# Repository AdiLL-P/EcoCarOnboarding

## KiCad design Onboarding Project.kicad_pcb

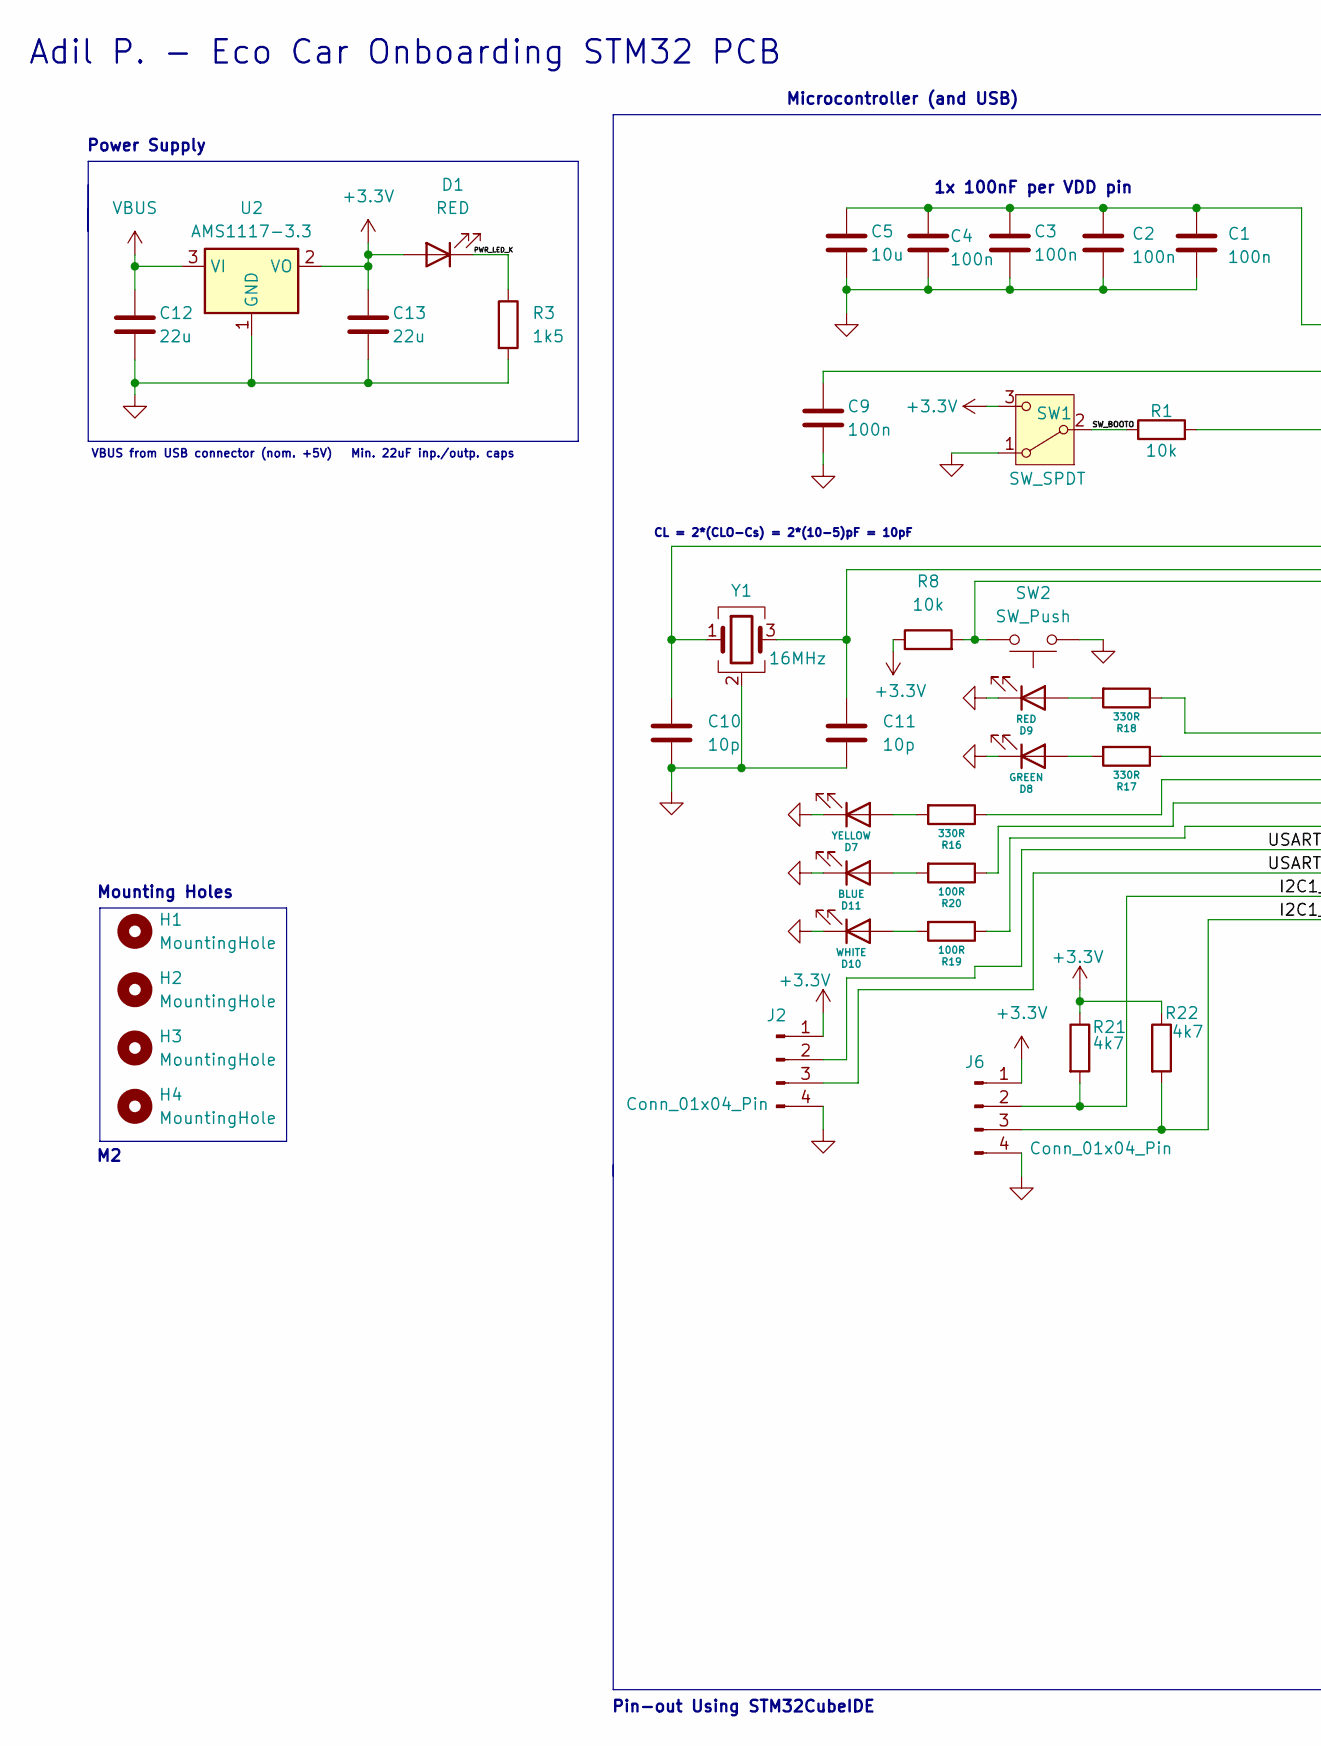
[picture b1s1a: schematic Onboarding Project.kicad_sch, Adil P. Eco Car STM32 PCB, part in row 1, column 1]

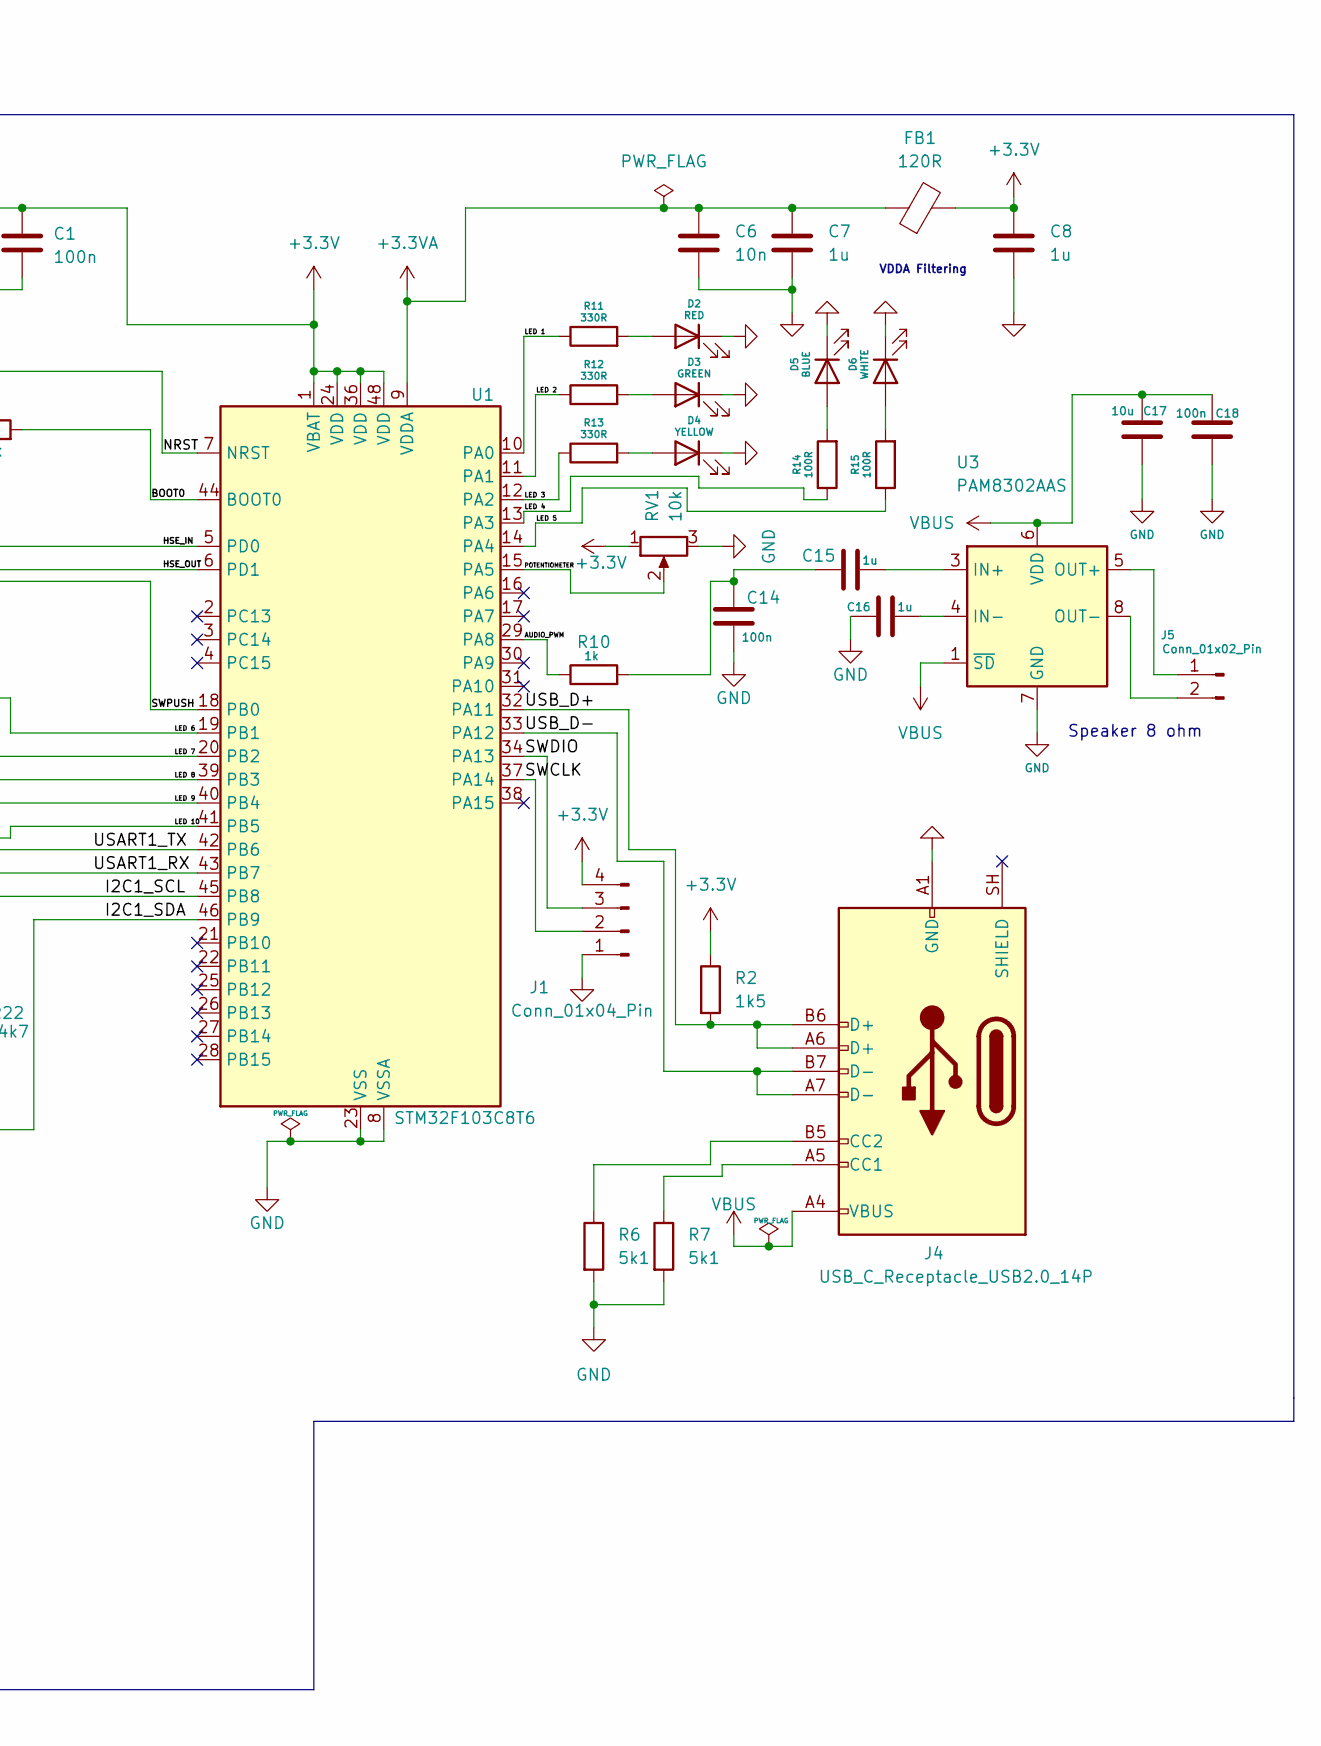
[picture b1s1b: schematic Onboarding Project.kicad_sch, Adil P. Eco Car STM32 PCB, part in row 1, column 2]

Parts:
C1, C2, C3, C4, C9, C14, C18: 100n; C_0402_1005Metric
C5, C17: 10u; C_0603_1608Metric
C6: 10n; C_0402_1005Metric
C7, C8, C15, C16: 1u; C_0402_1005Metric
C10, C11: 10p; C_0402_1005Metric
C12, C13: 22u; C_0805_2012Metric
D1, D2, D9: RED; LED_0603_1608Metric
D3, D8: GREEN; LED_0603_1608Metric
D4, D7: YELLOW; LED_0603_1608Metric
D5, D11: BLUE; LED_0603_1608Metric
D6, D10: WHITE; LED_0603_1608Metric
FB1: 120R; L_0603_1608Metric
H1, H2, H3, H4: MountingHole; MountingHole_2.2mm_M2
J1, J2, J6: Conn_01x04_Pin; PinHeader_1x04_P2.54mm_Vertical
J4: USB_C_Receptacle_USB2.0_14P; USB_C_Receptacle_HRO_TYPE-C-31-M-12
J5: Conn_01x02_Pin; PinHeader_1x02_P2.54mm_Vertical
R1, R8: 10k; R_0402_1005Metric
R2, R3: 1k5; R_0402_1005Metric
R6, R7: 5k1; R_0402_1005Metric
R10: 1k; R_0402_1005Metric
R11, R12, R13, R16, R17, R18: 330R; R_0603_1608Metric
R14, R15, R19, R20: 100R; R_0603_1608Metric
R21, R22: 4k7; R_0603_1608Metric
RV1: 10k; TSSOP-14_4.4x5mm_P0.65mm
SW1: SW_SPDT; SW_SPDT_PCM12
SW2: SW_Push; SW_NKK_GW12LJP
U1: STM32F103C8T6; LQFP-48_7x7mm_P0.5mm
U2: AMS1117-3.3; SOT-223-3_TabPin2
U3: PAM8302AAS; SOIC-8_3.9x4.9mm_P1.27mm
Y1: 16MHz; Crystal_SMD_3225-4Pin_3.2x2.5mm

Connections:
+3.3V: C1.1, C2.1, C3.1, C4.1, C5.1, C8.1, C13.1, D1.2 (A), FB1.2, J1.4, J2.1, J6.1, R2.1, R8.1, R21.1, R22.1, RV1.1, SW1.3 (C), U1.1 (VBAT), U1.24 (VDD), U1.36 (VDD), U1.48 (VDD), U2.2 (VO)
+3.3VA: C6.1, C7.1, FB1.1, U1.9 (VDDA)
/AUDIO_PWM: R10.1, U1.29 (PA8)
/BOOT0: R1.2, U1.44 (BOOT0)
/HSE_IN: C10.1, U1.5 (PD0), Y1.1
/HSE_OUT: C11.1, U1.6 (PD1), Y1.3
/I2C1_SCL: J6.2, R21.2, U1.45 (PB8)
/I2C1_SDA: J6.3, R22.2, U1.46 (PB9)
/LED 1: R11.1, U1.10 (PA0)
/LED 2: R12.1, U1.11 (PA1)
/LED 3: R13.1, U1.12 (PA2)
/LED 4: R14.1, U1.13 (PA3)
/LED 5: R15.1, U1.14 (PA4)
/LED 6: R18.1, U1.19 (PB1)
/LED 7: R17.1, U1.20 (PB2)
/LED 8: R16.1, U1.39 (PB3)
/LED 9: R20.1, U1.40 (PB4)
/LED 10: R19.1, U1.41 (PB5)
/NRST: C9.1, U1.7 (NRST)
/POTENTIOMETER: RV1.2, U1.15 (PA5)
/PWR_LED_K: D1.1 (K), R3.1
/SWCLK: J1.2, U1.37 (PA14)
/SWDIO: J1.3, U1.34 (PA13)
/SWPUSH: R8.2, SW2.2, U1.18 (PB0)
/SW_BOOTO: R1.1, SW1.2 (B)
/USART1_RX: J2.3, U1.43 (PB7)
/USART1_TX: J2.2, U1.42 (PB6)
/USB_D+: J4.A6 (D+), J4.B6 (D+), R2.2, U1.32 (PA11)
/USB_D-: J4.A7 (D-), J4.B7 (D-), U1.33 (PA12)
GND: C1.2, C2.2, C3.2, C4.2, C5.2, C6.2, C7.2, C8.2, C9.2, C10.2, C11.2, C12.2, C13.2, C14.2, C16.1, C17.1, C18.1, D2.1 (K), D3.1 (K), D4.1 (K), D5.1 (K), D6.1 (K), D7.1 (K), D8.1 (K), D9.1 (K), D10.1 (K), D11.1 (K), J1.1, J2.4, J4.A1 (GND), J4.A12 (GND), J4.B1 (GND), J4.B12 (GND), J6.4, R3.2, R6.2, R7.2, RV1.3, SW1.1 (A), SW2.1, U1.8 (VSSA), U1.23 (VSS), U1.35 (VSS), U1.47 (VSS), U2.1 (GND), U3.7 (GND), Y1.2 (G), Y1.4 (G)
unnamed: C14.1, C15.1, R10.2
unnamed: D2.2 (A), R11.2
unnamed: D3.2 (A), R12.2
unnamed: D4.2 (A), R13.2
unnamed: D5.2 (A), R14.2
unnamed: D6.2 (A), R15.2
unnamed: D7.2 (A), R16.2
unnamed: D8.2 (A), R17.2
unnamed: D9.2 (A), R18.2
unnamed: D10.2 (A), R19.2
unnamed: D11.2 (A), R20.2
unnamed: J4.A5 (CC1), R7.1
unnamed: J4.B5 (CC2), R6.1
unnamed: J5.1, U3.5 (OUT+)
unnamed: J5.2, U3.8 (OUT-)
unnamed: C15.2, U3.3 (IN+)
unnamed: C16.2, U3.4 (IN-)
VBUS: C12.1, C17.2, C18.2, J4.A4 (VBUS), J4.A9 (VBUS), J4.B4 (VBUS), J4.B9 (VBUS), U2.3 (VI), U3.1 (~SD), U3.6 (VDD)

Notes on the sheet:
Pin-out Using STM32CubeIDE
Adil P. - Eco Car Onboarding STM32 PCB
1x 100nF per VDD pin
Mounting Holes
Speaker 8 ohm
Microcontroller (and USB)
Power Supply
VDDA Filtering
CL = 2*(CLO-Cs) = 2*(10-5)pF = 10pF
VBUS from USB connector (nom. +5V) Min. 22uF inp./outp. caps

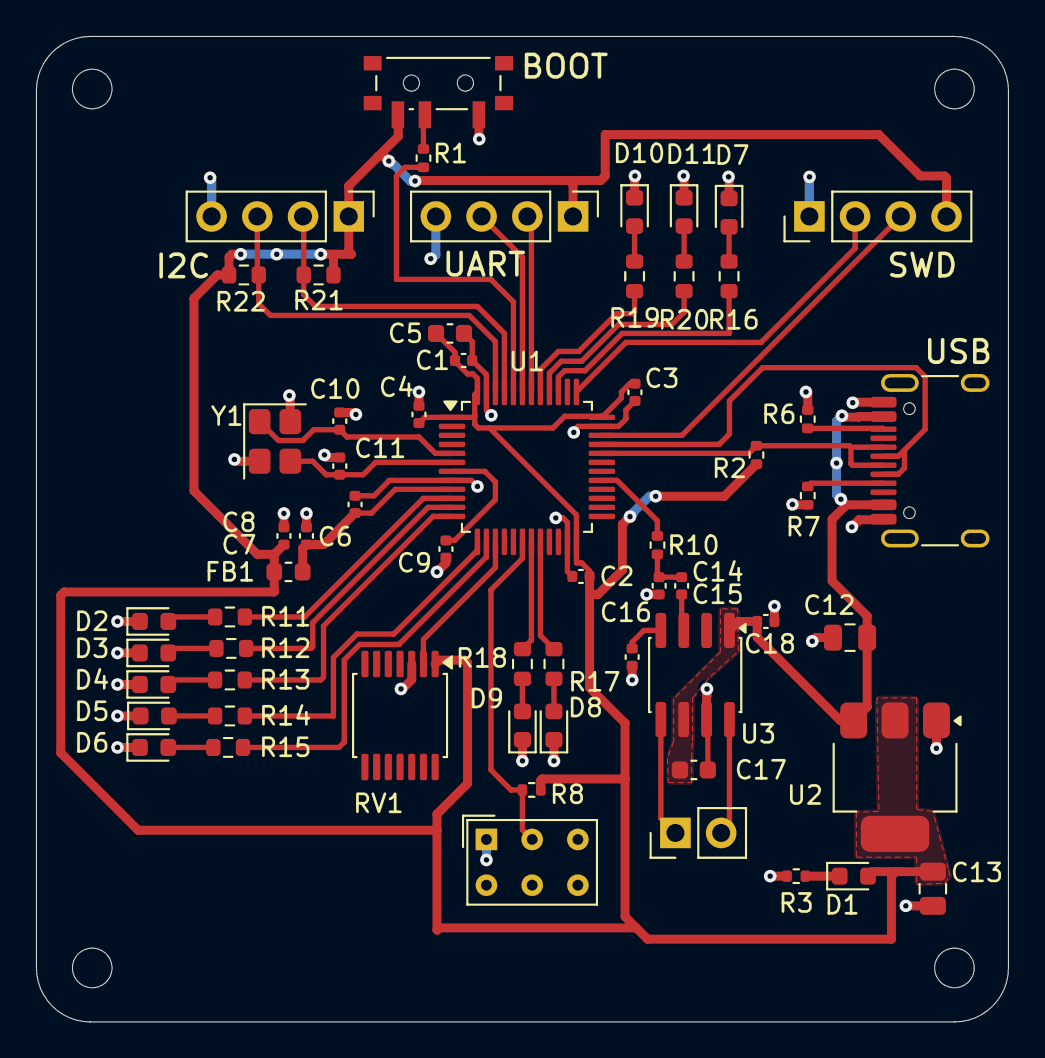
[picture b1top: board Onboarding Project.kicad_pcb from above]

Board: 2 copper layers, 54.0 x 54.8 mm, 65 parts (0 on the bottom side), 48 nets.

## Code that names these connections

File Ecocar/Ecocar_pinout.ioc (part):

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Mcu.Name=STM32F103C(8-B)Tx
Mcu.Package=LQFP48
Mcu.UserName=STM32F103C8Tx
PA11.Mode=Device
PA11.Signal=USB_DM
PA12.Mode=Device
PA12.Signal=USB_DP
PA13.Mode=Serial_Wire
PA13.Signal=SYS_JTMS-SWDIO
PA14.Mode=Serial_Wire
PA14.Signal=SYS_JTCK-SWCLK
PB10.Mode=I2C
PB10.Signal=I2C2_SCL
PB11.Mode=I2C
PB11.Signal=I2C2_SDA
PB13.Mode=Full_Duplex_Master
PB13.Signal=SPI2_SCK
PB14.Mode=Full_Duplex_Master
PB14.Signal=SPI2_MISO
PB15.Mode=Full_Duplex_Master
PB15.Signal=SPI2_MOSI
PB6.Mode=Asynchronous
PB6.Signal=USART1_TX
PB7.Mode=Asynchronous
PB7.Signal=USART1_RX
PB8.Mode=I2C
PB8.Signal=I2C1_SCL
PB9.Mode=I2C
PB9.Signal=I2C1_SDA
PD0-OSC_IN.Mode=HSE-External-Oscillator
PD0-OSC_IN.Signal=RCC_OSC_IN
PD1-OSC_OUT.Mode=HSE-External-Oscillator
PD1-OSC_OUT.Signal=RCC_OSC_OUT
RCC.SYSCLKFreq_VALUE=8000000
board=custom
